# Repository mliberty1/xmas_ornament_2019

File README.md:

# Introduction

This repository contains the hardware and software for the ornament designed
for Christmas 2019.  The ornament contains LEDs that illuminate through the
circuit board.  The LEDs are controlled by a SAMD21 processor running Arduino
code.  The ornament looks like this:

# Configuration

This project is based upon the Arduino Zero, specifically the [Adafruit
Feather M0 Basic](https://learn.adafruit.com/adafruit-feather-m0-basic-proto/using-with-arduino-ide)
with the Adafruit bootloader.

https://adafruit.github.io/arduino-board-index/package_adafruit_index.json

Add Arduino SAMD21 boards.

Unfortunately, I used pins that did not normally have PWM (analogWrite) 
support.  So, I hacked the board variant definition so that it does.  For now,
you can replace the Feather M0 Express definition:

    cp arduino\variant.cpp "%LOCALAPPDATA%\Arduino15\packages\adafruit\hardware\samd\1.5.7\variants\feather_m0_express\variant.cpp"

## Manufacturing

* Surface mount all parts except LEDs and battery holder.
* Manually solder LEDs facing "wrong way".
* Manually solder battery holder.
* Program the [bootloader](https://learn.adafruit.com/how-to-program-samd-bootloaders).
* Program the Arduino program.

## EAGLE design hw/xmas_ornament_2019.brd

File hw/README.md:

https://gfwilliams.github.io/svgtoeagle/

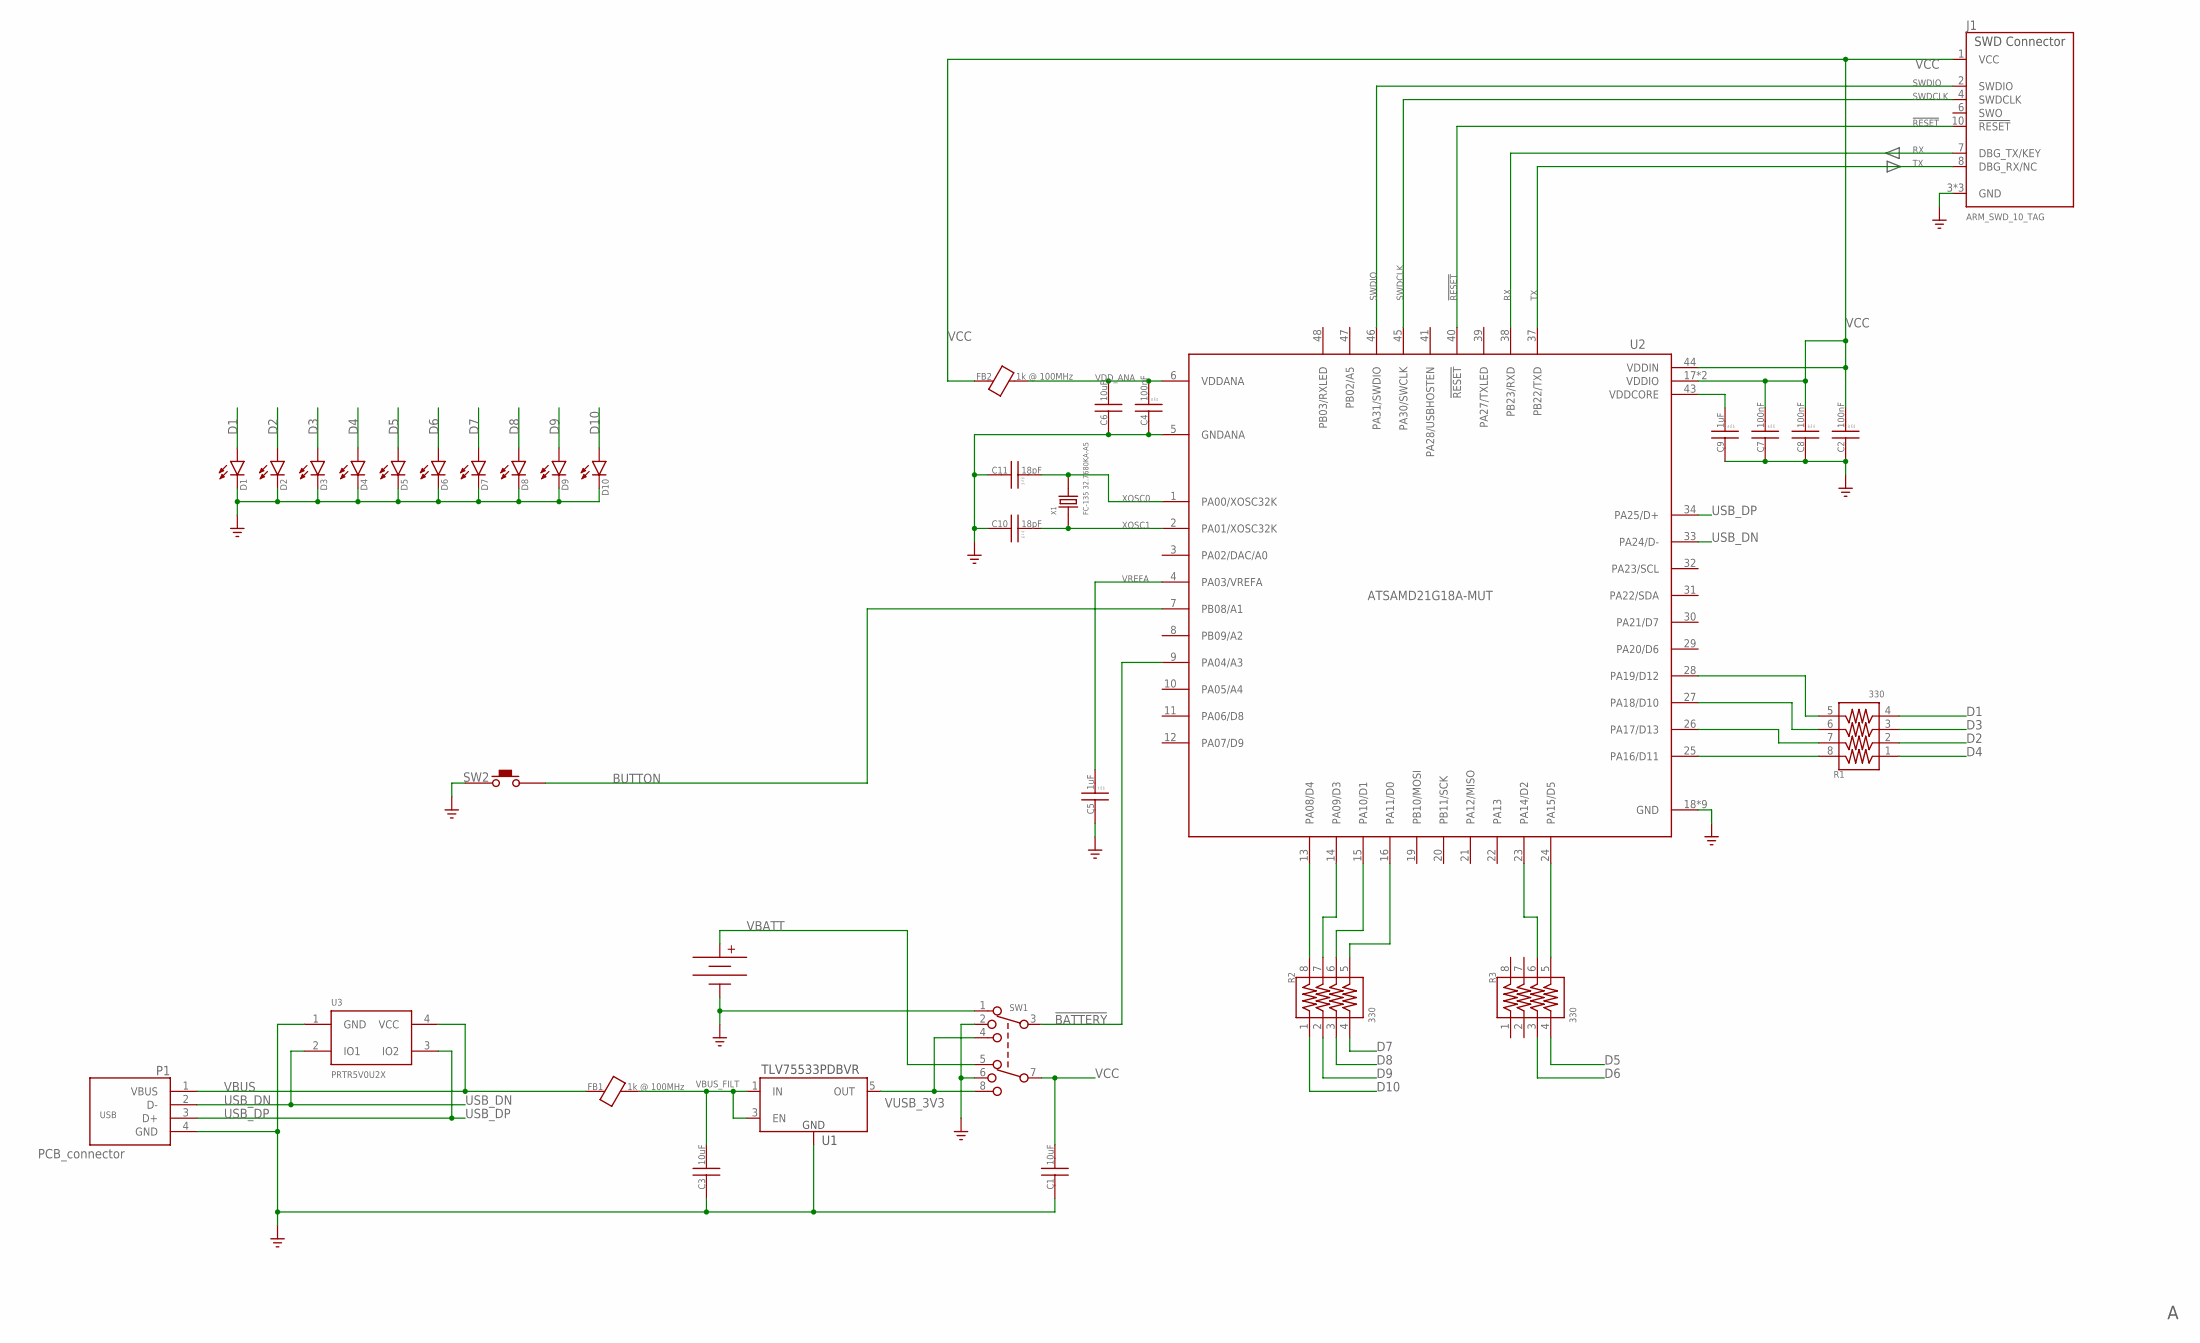
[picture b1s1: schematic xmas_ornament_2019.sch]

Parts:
C1, C3, C6: 10uF; 0805; TOLERANCE 20%; VOLTAGE 6.3V; MPN JMK212AB7106KGHT
C2, C4, C7, C8: 100nF; 0603; TOLERANCE 20%; VOLTAGE 50V; MPN CC0603KRX7R9BB104
C5, C9: 1uF; 0603; TOLERANCE 20%; VOLTAGE 10V; MPN CC0603KRX5R6BB105
C10, C11: 18pF; 0603; TOLERANCE 5%; VOLTAGE 50V; MPN GRM1885C1H220JA01D
D1, D2, D3, D4, D5, D6, D7, D8, D9, D10: APT2012LSYCK/J3-PRV; LED_0805_BREV; MPN APT2012LSYCK/J3-PRV
FB1, FB2: 1k @ 100MHz; 0603; MPN 742792663
J1: ARM_SWD_10_TAG; TC2050-IDC-NL
J2: BU2450-SM-JJ-GTR; BU2450SM-JJ-GTR; MPN BU2450-SM-JJ-GTR
P1: PCB_connector; USB-A_PCB
R1, R2, R3: 330; 1206X4; TOLERANCE 5%; MPN EXB-38V331JV
SW1: JS203011SCQN; MPN JS203011SCQN
SW2: PTS645SM43SMTR92 LFS; SWITCH_6MM; MPN PTS645SM43SMTR92 LFS
U1: TLV75533PDBVR; SOT23-5; MPN TLV75533PDBVR
U2: ATSAMD21G18A-MUT; QFN-48_GND
U3: PRTR5V0U2X; SOT143B; MPN PRTR5V0U2X,215
X1: FC-135 32.7680KA-A5; XTAL_3.2X1.5

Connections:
!BATTERY: SW1.3 (A_COM), U2.9 (PA04/A3)
!RESET: J1.10 (!RESET), U2.40 (!RESET)
BUTTON: SW2.1, SW2.2, U2.7 (PB08/A1)
D1: D1.A, R1.4 (4A)
D2: D2.A, R1.2 (2A)
D3: D3.A, R1.3 (3A)
D4: D4.A, R1.1 (1A)
D5: D5.A, R3.4 (4A)
D6: D6.A, R3.3 (3A)
D7: D7.A, R2.4 (4A)
D8: D8.A, R2.3 (3A)
D9: D9.A, R2.2 (2A)
D10: D10.A, R2.1 (1A)
GND: C1.1, C2.1, C3.1, C4.1, C5.1, C6.1, C7.1, C8.1, C9.1, C10.1, C11.1, D1.C, D2.C, D3.C, D4.C, D5.C, D6.C, D7.C, D8.C, D9.C, D10.C, J1.3 (GND), J1.5 (GND), J1.9 (GND), J2.-, P1.4 (GND), SW1.1 (A1), SW1.2 (A2), SW1.6 (B2), SW2.3, SW2.4, U1.2 (GND), U2.5 (GNDANA), U2.18 (GND), U2.35 (GND), U2.42 (GND), U2.GND, U2.GND@A (GND), U2.GND@A1 (GND), U2.GND@A2 (GND), U2.GND@A3 (GND), U2.GND@A4 (GND), U3.1 (GND)
unnamed: R2.8 (1B), U2.13 (PA08/D4)
unnamed: R2.7 (2B), U2.14 (PA09/D3)
unnamed: R2.6 (3B), U2.15 (PA10/D1)
unnamed: C9.2, U2.43 (VDDCORE)
unnamed: R2.5 (4B), U2.16 (PA11/D0)
unnamed: R1.8 (1B), U2.25 (PA16/D11)
unnamed: R1.7 (2B), U2.26 (PA17/D13)
unnamed: R1.5 (4B), U2.28 (PA19/D12)
unnamed: R1.6 (3B), U2.27 (PA18/D10)
unnamed: R3.5 (4B), U2.24 (PA15/D5)
unnamed: R3.6 (3B), U2.23 (PA14/D2)
RX: J1.7 (DBG_TX/KEY), U2.38 (PB23/RXD)
SWDCLK: J1.4 (SWDCLK), U2.45 (PA30/SWCLK)
SWDIO: J1.2 (SWDIO), U2.46 (PA31/SWDIO)
TX: J1.8 (DBG_RX/NC), U2.37 (PB22/TXD)
USB_DN: P1.2 (D-), U2.33 (PA24/D-), U3.2 (IO1)
USB_DP: P1.3 (D+), U2.34 (PA25/D+), U3.3 (IO2)
VBATT: J2.+, SW1.5 (B1)
VBUS: FB1.1, P1.1 (VBUS), U3.4 (VCC)
VBUS_FILT: C3.2, FB1.2, U1.1 (IN), U1.3 (EN)
VCC: C1.2, C2.2, C7.2, C8.2, FB2.1, J1.1 (VCC), SW1.7 (B_COM), U2.17 (VDDIO), U2.36 (VDDIO), U2.44 (VDDIN)
VDD_ANA: C4.2, C6.2, FB2.2, U2.6 (VDDANA)
VREFA: C5.2, U2.4 (PA03/VREFA)
VUSB_3V3: SW1.4 (A3), SW1.8 (B3), U1.5 (OUT)
XOSC0: C11.2, U2.1 (PA00/XOSC32K), X1.2
XOSC1: C10.2, U2.2 (PA01/XOSC32K), X1.1

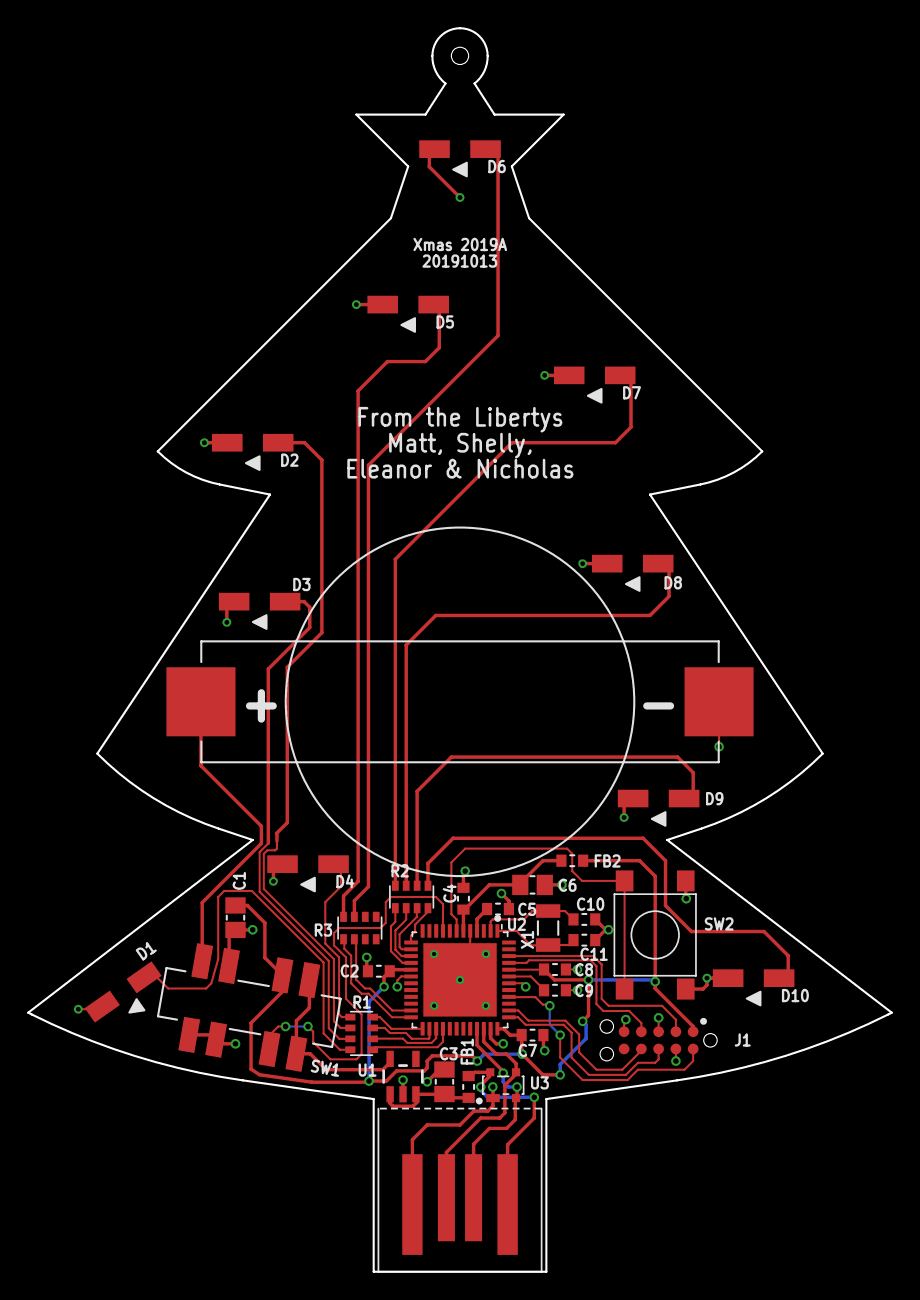
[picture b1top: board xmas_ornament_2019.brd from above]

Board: 2 copper layers, 63.5 x 91.4 mm, 35 parts (0 on the bottom side), 40 nets.

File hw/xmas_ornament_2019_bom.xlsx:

xmas_ornament_2019 rev A BOM
2019 November 17
# | Ref Des | Qty | Value | Package | Description | Mfg | Mfg Part # | Notes
1 | R1, R2, R3 | 3 | 330 | 4_1206 | 5%,200 ppm/°C,0.062W | Panasonic | EXB-38V331JV
2 | C10, C11 | 2 | 18p | 0603 | 5%,C0G,50V | Murata | GRM1885C1H180JA01D
3 | C2, C4, C7, C8 | 4 | 100n | 0603 | 20%,X5R,50V | Yageo | CC0603KRX7R9BB104
4 | C5, C9 | 2 | 1µ | 0603 | 20%,X5R,10V | Yageo | CC0603KRX5R6BB105
5 | C1, C3, C6 | 3 | 10µ | 0805 | 20%,X7R,6.3V | Taiyo Yuden | JMK212AB7106KGHT
6 | FB1, FB2 | 2 |  | 0603 |  | Wurth | 742792663
7 | D1, D2, D3, D4, D5, D6, D7, D8, D9, D10 | 10 |  | 0805 |  | Kingbright | APT2012LSYCK/J3-PRV
8 | X1 | 1 |  | 3.2x1.5mm |  | Epson | FC-135 32.7680KA-A5
9 | U3 | 1 |  | TO-253-4 |  | Nexperia | PRTR5V0U2X,215
10 | U2 | 1 |  | QFN-48 |  | Microchip | ATSAMD21G18A-MUT
11 | U1 | 1 |  | SOT-23-5 |  | TI | TLV75533PDBVR
12 | J2 | 1 |  |  |  | MPD | BU2450-SM-JJ-GTR
13 | SW2 | 1 |  |  |  | C&K | PTS645SM43SMTR92 LFS
14 | SW1 | 1 |  |  |  | C&K | JS203011SCQN
 |  | 33

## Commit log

2019-10-27 Board in progress.
2019-11-16 Current progress.
2019-11-16 Added artwork
2019-11-17 Rev A.
2019-12-10 Added initial Arduino sketch.
2019-12-10 Analog PWM working.
2019-12-11 Working async animations.
2019-12-11 Refactored code to simplify INO.
2019-12-11 Added documentation and todos.
2019-12-11 Added led_delay_random
2019-12-11 Refactored button.
2019-12-11 Added Nicholas's first test.
2019-12-11 Start next LED command immediately on done.
2019-12-11 Improved patterns and changed durations.
2019-12-12 Added images and updated readme.
2019-12-16 Fixed fading to dimmer on TC using interrupts to implement software "double-buffer".
2019-12-17 Added low-power sleep and additional blink patterns.
2019-12-30 Added patterns requested by family.
